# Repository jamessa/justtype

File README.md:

# Justtype

一把字型設計師專用的單手鍵盤

Designed by Bold and James. Manufactured by [Pragmatic Inc](www.pragmatic.com.tw)

## Feature

- 鑽石方向鍵配置
- 支援左手或右手
- 容易組裝
- 人體工學配置

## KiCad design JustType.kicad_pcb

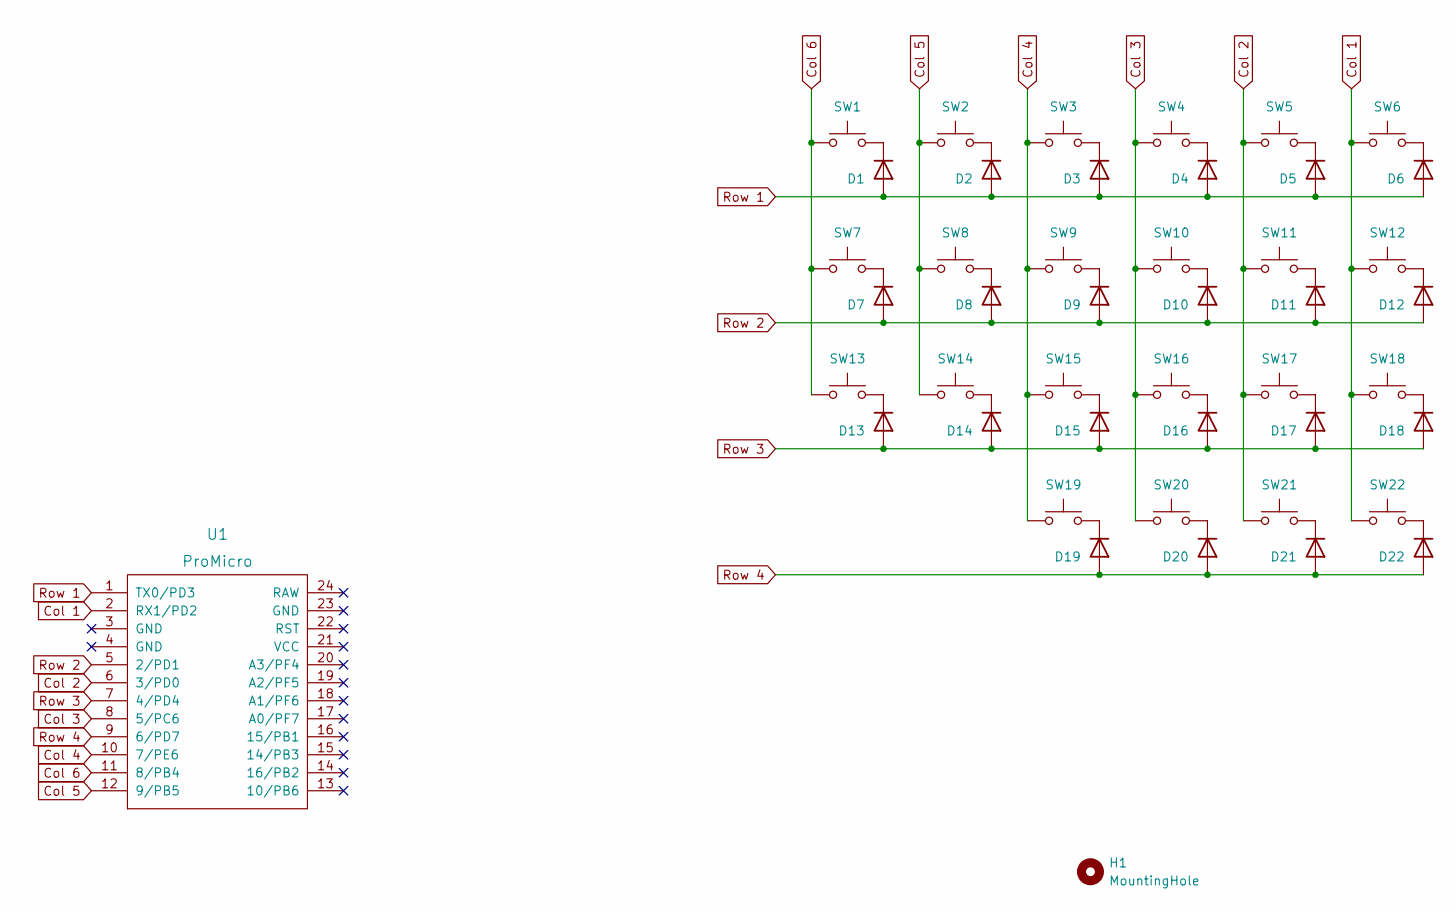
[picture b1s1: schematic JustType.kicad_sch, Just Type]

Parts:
D1, D2, D3, D4, D5, D6, D7, D8, D9, D10, D11, D12, D13, D14, D15, D16, D17, D18, D19, D20, D21, D22: 1N4448W; D3_SMD_v2_Reverse
H1: MountingHole; MountingHole_3.2mm_M3
SW1, SW2, SW3, SW4, SW5, SW6, SW7, SW8, SW9, SW10, SW11, SW12, SW13, SW14, SW15, SW16, SW17, SW18, SW19, SW20, SW21, SW22: SW_Push; ChocV2_Solder_2side_v1
U1: ProMicro; ArduinoProMicro

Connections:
Col 1: SW6.1, SW12.1, SW18.1, SW22.1, U1.2 (RX1/PD2)
Col 2: SW5.1, SW11.1, SW17.1, SW21.1, U1.6 (3/PD0)
Col 3: SW4.1, SW10.1, SW16.1, SW20.1, U1.8 (5/PC6)
Col 4: SW3.1, SW9.1, SW15.1, SW19.1, U1.10 (7/PE6)
Col 5: SW2.1, SW8.1, SW14.1, U1.12 (9/PB5)
Col 6: SW1.1, SW7.1, SW13.1, U1.11 (8/PB4)
unnamed: D1.1 (K), SW1.2
unnamed: D2.1 (K), SW2.2
unnamed: D3.1 (K), SW3.2
unnamed: D4.1 (K), SW4.2
unnamed: D5.1 (K), SW5.2
unnamed: D6.1 (K), SW6.2
unnamed: D7.1 (K), SW7.2
unnamed: D8.1 (K), SW8.2
unnamed: D9.1 (K), SW9.2
unnamed: D10.1 (K), SW10.2
unnamed: D11.1 (K), SW11.2
unnamed: D12.1 (K), SW12.2
unnamed: D13.1 (K), SW13.2
unnamed: D14.1 (K), SW14.2
unnamed: D15.1 (K), SW15.2
unnamed: D16.1 (K), SW16.2
unnamed: D17.1 (K), SW17.2
unnamed: D18.1 (K), SW18.2
unnamed: D19.1 (K), SW19.2
unnamed: D20.1 (K), SW20.2
unnamed: D21.1 (K), SW21.2
unnamed: D22.1 (K), SW22.2
Row 1: D1.2 (A), D2.2 (A), D3.2 (A), D4.2 (A), D5.2 (A), D6.2 (A), U1.1 (TX0/PD3)
Row 2: D7.2 (A), D8.2 (A), D9.2 (A), D10.2 (A), D11.2 (A), D12.2 (A), U1.5 (2/PD1)
Row 3: D13.2 (A), D14.2 (A), D15.2 (A), D16.2 (A), D17.2 (A), D18.2 (A), U1.7 (4/PD4)
Row 4: D19.2 (A), D20.2 (A), D21.2 (A), D22.2 (A), U1.9 (6/PD7)

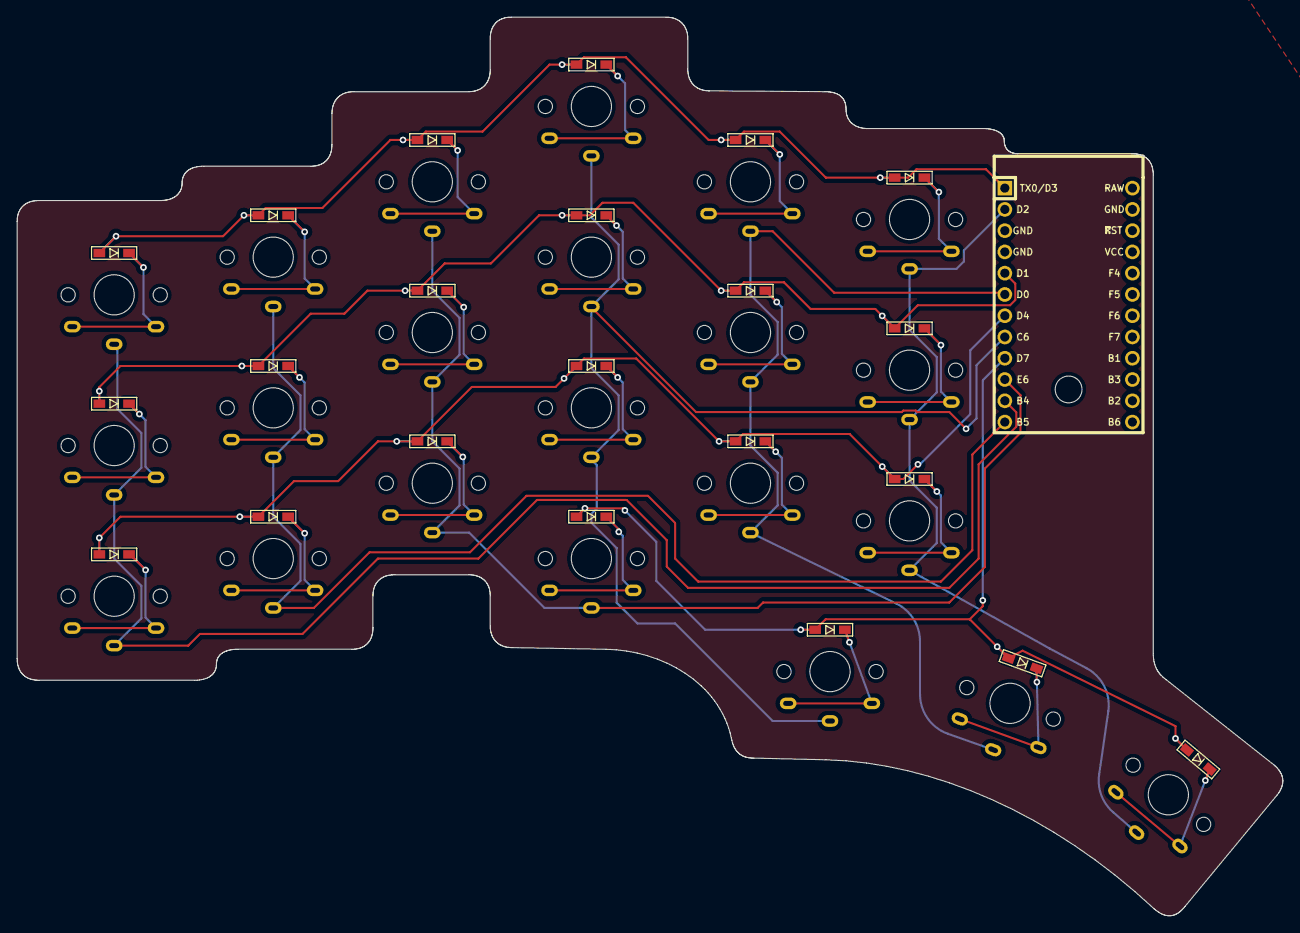
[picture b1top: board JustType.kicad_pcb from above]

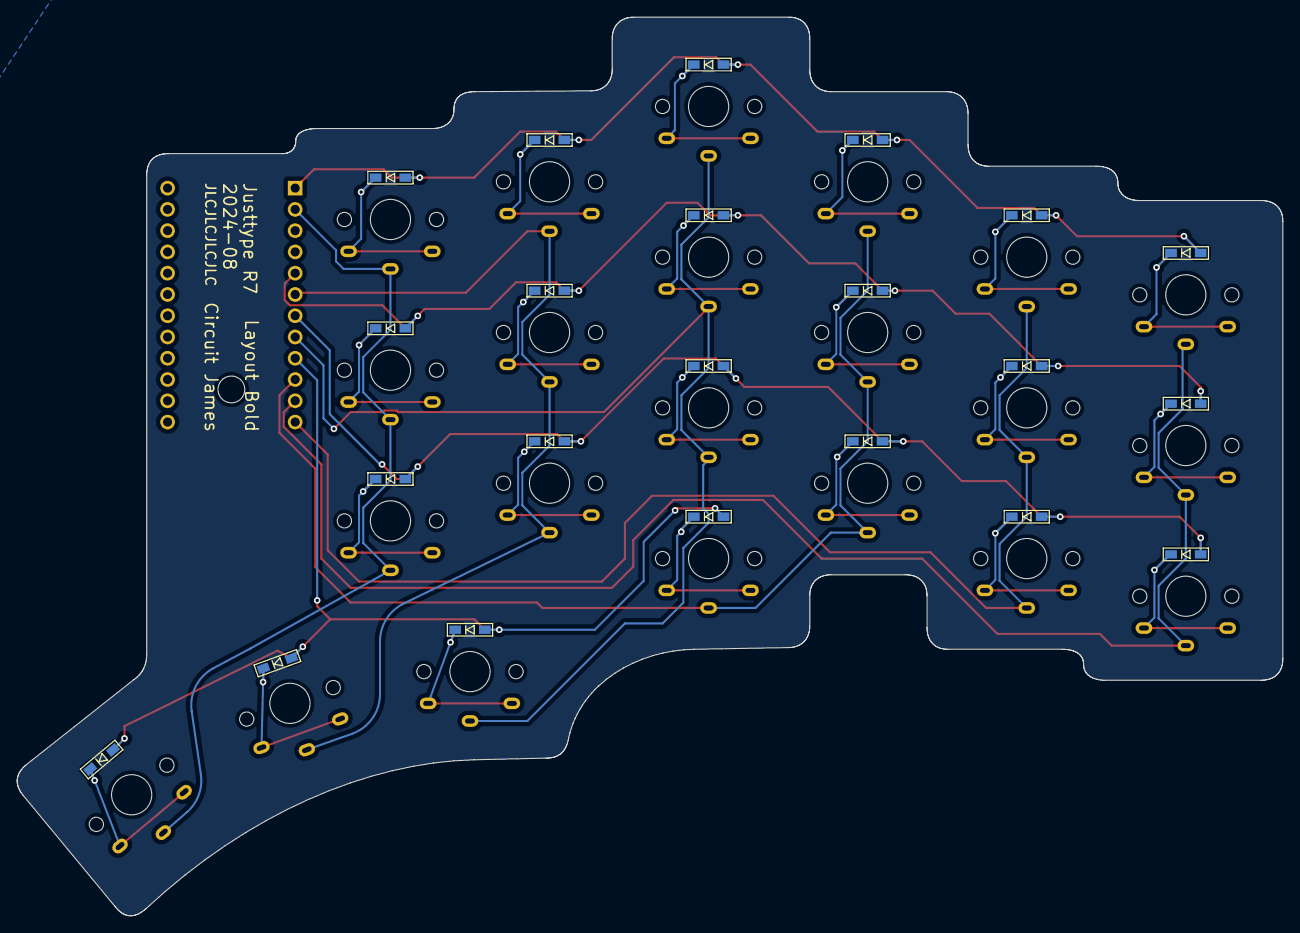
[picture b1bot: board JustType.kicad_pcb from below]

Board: 2 copper layers, 151.2 x 107.3 mm, 46 parts (22 on the bottom side), 32 nets.

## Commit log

2024-06-20 init
2024-08-11 R5 validated.
2024-08-28 validating
2024-10-31 📝 更新說明
